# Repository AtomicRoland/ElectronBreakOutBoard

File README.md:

# ElectronBreakOutBoard
The break out / riser board for the Electron provides a way to check the Electron Plus1 cartridge slot signals during developing and error tracing of (new) boards.

You may choose to mount the 44 pin header strip on either side of the board. Just notice that if you mount it at the keyboard side, then pin 1 is not really pin 1 any more!

To mount the edge connector slot, first bend the pins on both rows slightly until there is a gap of about 1.6 mm. Then push it over the top edge connector (near the header) and solder the pins on both sides. That’s all.

*Please unzip the file myelin-kicad.pretty-master.zip before opening the project in KiCad.*

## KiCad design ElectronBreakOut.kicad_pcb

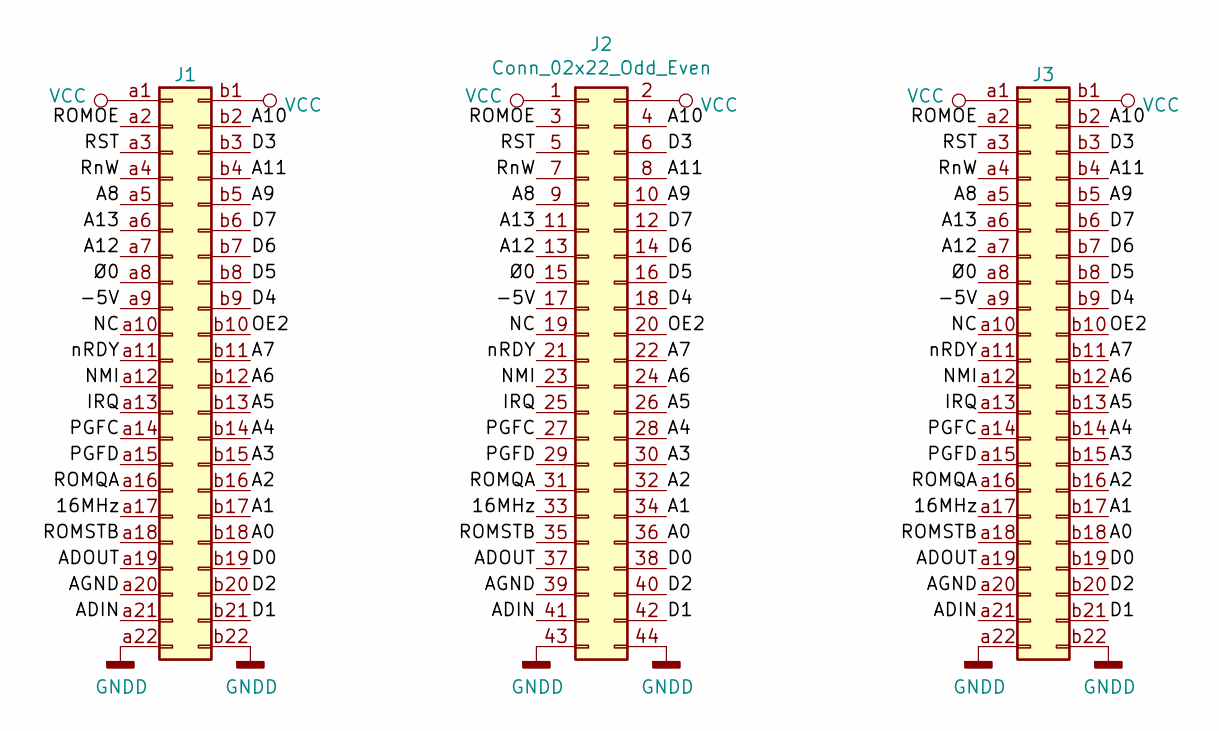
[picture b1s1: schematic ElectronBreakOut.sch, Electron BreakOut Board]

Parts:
J1: Conn_02x22_Row_Letter_First; acorn_electron_cartridge_edge_connector
J2: Conn_02x22_Odd_Even; PinHeader_2x22_P2.54mm_Vertical
J3: Conn_02x22_Row_Letter_First; acorn_electron_cartridge_edge_top

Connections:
/16MHz: J1.a17, J2.33, J3.a17
/-5V: J1.a9, J2.17, J3.a9
/A0: J1.b18, J2.36, J3.b18
/A1: J1.b17, J2.34, J3.b17
/A2: J1.b16, J2.32, J3.b16
/A3: J1.b15, J2.30, J3.b15
/A4: J1.b14, J2.28, J3.b14
/A5: J1.b13, J2.26, J3.b13
/A6: J1.b12, J2.24, J3.b12
/A7: J1.b11, J2.22, J3.b11
/A8: J1.a5, J2.9, J3.a5
/A9: J1.b5, J2.10, J3.b5
/A10: J1.b2, J2.4, J3.b2
/A11: J1.b4, J2.8, J3.b4
/A12: J1.a7, J2.13, J3.a7
/A13: J1.a6, J2.11, J3.a6
/ADIN: J1.a21, J2.41, J3.a21
/ADOUT: J1.a19, J2.37, J3.a19
/AGND: J1.a20, J2.39, J3.a20
/D0: J1.b19, J2.38, J3.b19
/D1: J1.b21, J2.42, J3.b21
/D2: J1.b20, J2.40, J3.b20
/D3: J1.b3, J2.6, J3.b3
/D4: J1.b9, J2.18, J3.b9
/D5: J1.b8, J2.16, J3.b8
/D6: J1.b7, J2.14, J3.b7
/D7: J1.b6, J2.12, J3.b6
/IRQ: J1.a13, J2.25, J3.a13
/NC: J1.a10, J2.19, J3.a10
/NMI: J1.a12, J2.23, J3.a12
/OE2: J1.b10, J2.20, J3.b10
/PGFC: J1.a14, J2.27, J3.a14
/PGFD: J1.a15, J2.29, J3.a15
/ROMOE: J1.a2, J2.3, J3.a2
/ROMQA: J1.a16, J2.31, J3.a16
/ROMSTB: J1.a18, J2.35, J3.a18
/RST: J1.a3, J2.5, J3.a3
/RnW: J1.a4, J2.7, J3.a4
/nRDY: J1.a11, J2.21, J3.a11
/Ø0: J1.a8, J2.15, J3.a8
GNDD: J1.a22, J1.b22, J2.43, J2.44, J3.a22, J3.b22
VCC: J1.a1, J1.b1, J2.1, J2.2, J3.a1, J3.b1

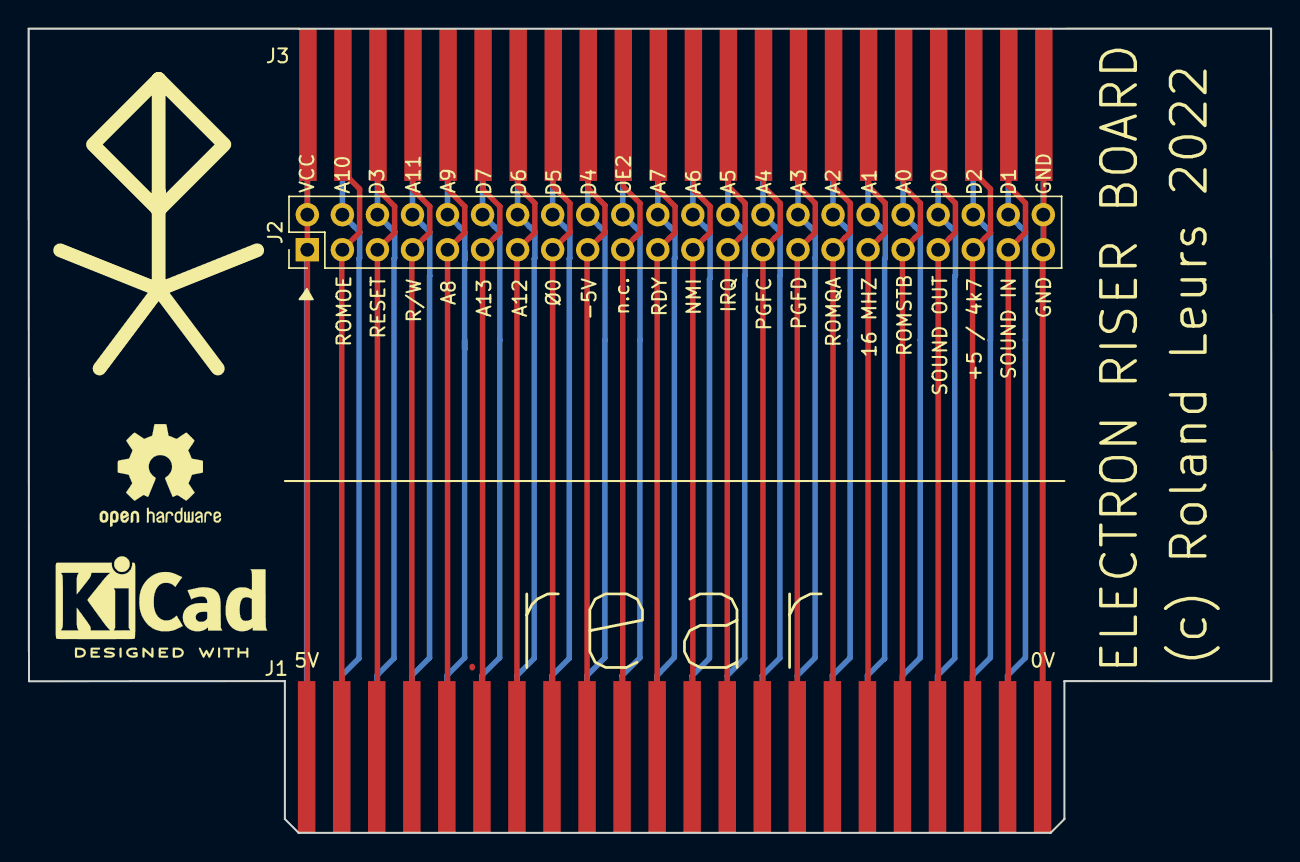
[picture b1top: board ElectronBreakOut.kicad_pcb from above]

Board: 2 copper layers, 90.1 x 58.3 mm, 3 parts (0 on the bottom side), 42 nets.

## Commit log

2022-08-28 Upload of initial files (production MK1)
